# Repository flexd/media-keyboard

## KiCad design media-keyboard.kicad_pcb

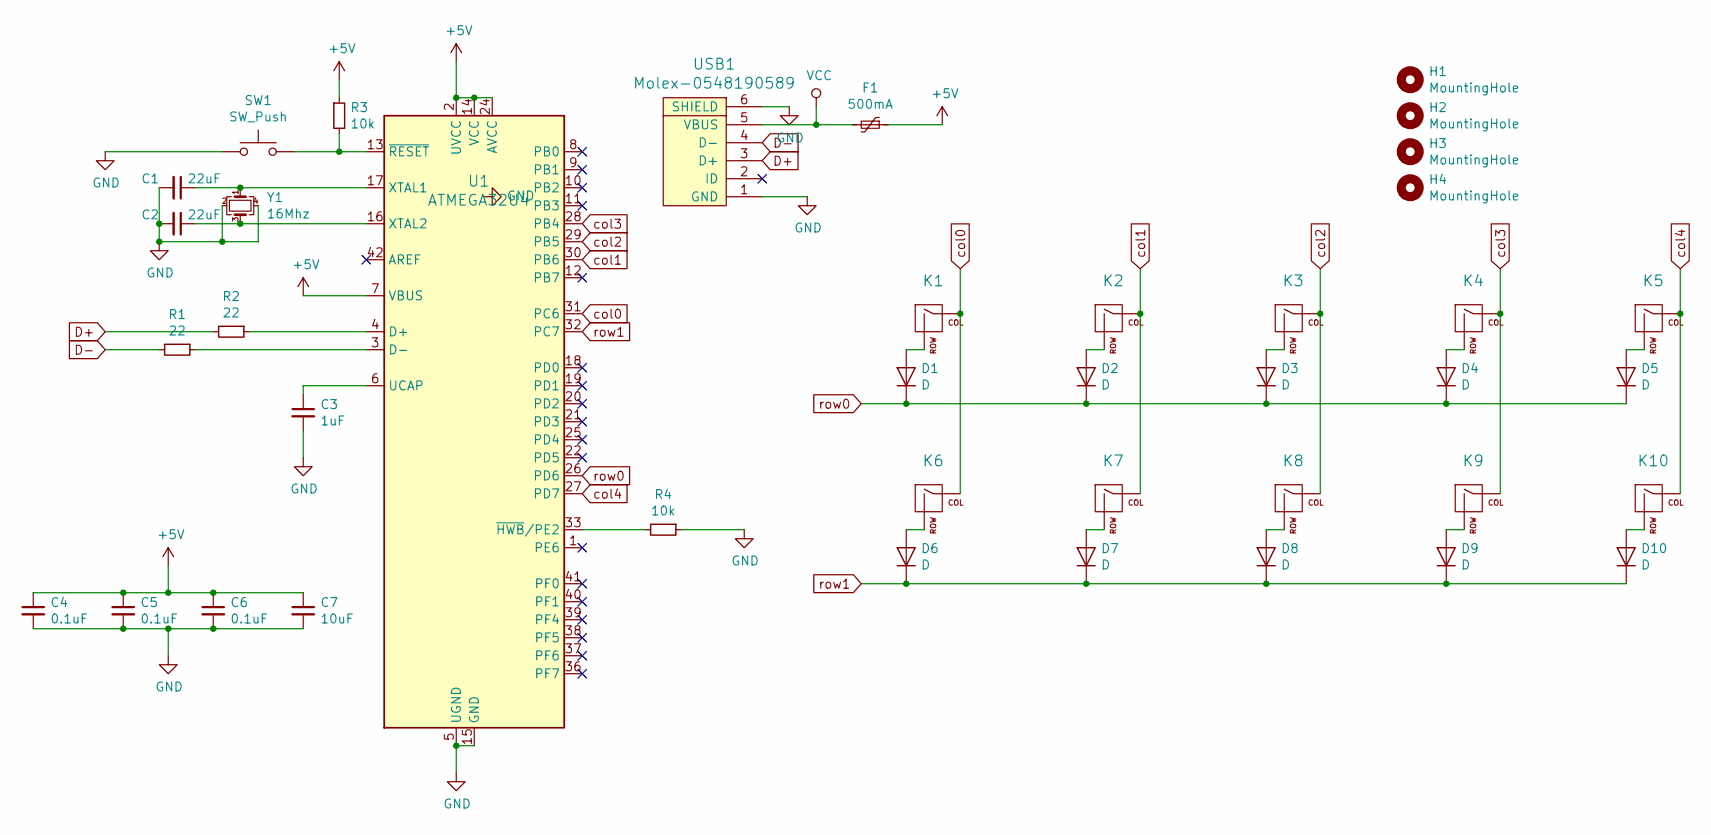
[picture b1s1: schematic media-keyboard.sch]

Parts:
C1, C2: 22uF; C_0805_2012Metric_Pad1.15x1.40mm_HandSolder
C3: 1uF; C_0805_2012Metric_Pad1.15x1.40mm_HandSolder
C4, C5, C6: 0.1uF; C_0805_2012Metric_Pad1.15x1.40mm_HandSolder
C7: 10uF; C_0805_2012Metric_Pad1.15x1.40mm_HandSolder
D1, D2, D3, D4, D5, D6, D7, D8, D9, D10: D; D_SOD-123
F1: 500mA; Fuse_1206_3216Metric
H1, H2, H3, H4: MountingHole; MountingHole_2.2mm_M2
K1, K2, K3, K4, K5, K6, K7, K8, K9, K10: KEYSW; MX-1U-NoLED
R1, R2: 22; R_0805_2012Metric_Pad1.15x1.40mm_HandSolder
R3, R4: 10k; R_0805_2012Metric_Pad1.15x1.40mm_HandSolder
SW1: SW_Push; SKQG-1155865
U1: ATMEGA32U4; TQFP-44_10x10mm_P0.8mm
USB1: Molex-0548190589
Y1: 16Mhz; Crystal_SMD_3225-4Pin_3.2x2.5mm

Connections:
+5V: C4.1, C5.1, C6.1, C7.1, F1.1, R3.1, U1.2 (UVCC), U1.7 (VBUS), U1.14 (VCC), U1.24 (AVCC), U1.34 (VCC), U1.44 (AVCC)
D+: R2.2, USB1.3 (D+)
D-: R1.2, USB1.4 (D-)
GND: C1.2, C2.2, C3.2, C4.2, C5.2, C6.2, C7.2, R4.1, SW1.1, U1.5 (UGND), U1.15 (GND), U1.23 (GND), U1.35 (GND), U1.43 (GND), USB1.1 (GND), USB1.6 (SHIELD), Y1.2, Y1.4
unnamed: C1.1, U1.17 (XTAL1), Y1.1
unnamed: C2.1, U1.16 (XTAL2), Y1.3
unnamed: C3.1, U1.6 (UCAP)
unnamed: D1.2 (A), K1.2 (ROW)
unnamed: D2.2 (A), K2.2 (ROW)
unnamed: D3.2 (A), K3.2 (ROW)
unnamed: D4.2 (A), K4.2 (ROW)
unnamed: D5.2 (A), K5.2 (ROW)
unnamed: D6.2 (A), K6.2 (ROW)
unnamed: D7.2 (A), K7.2 (ROW)
unnamed: D8.2 (A), K8.2 (ROW)
unnamed: D9.2 (A), K9.2 (ROW)
unnamed: D10.2 (A), K10.2 (ROW)
unnamed: R1.1, U1.3 (D-)
unnamed: R2.1, U1.4 (D+)
unnamed: R3.2, SW1.2, U1.13 (~RESET)
unnamed: R4.2, U1.33 (~HWB~/PE2)
VCC: F1.2, USB1.5 (VBUS)
col0: K1.1 (COL), K6.1 (COL), U1.31 (PC6)
col1: K2.1 (COL), K7.1 (COL), U1.30 (PB6)
col2: K3.1 (COL), K8.1 (COL), U1.29 (PB5)
col3: K4.1 (COL), K9.1 (COL), U1.28 (PB4)
col4: K5.1 (COL), K10.1 (COL), U1.27 (PD7)
row0: D1.1 (K), D2.1 (K), D3.1 (K), D4.1 (K), D5.1 (K), U1.26 (PD6)
row1: D6.1 (K), D7.1 (K), D8.1 (K), D9.1 (K), D10.1 (K), U1.32 (PC7)

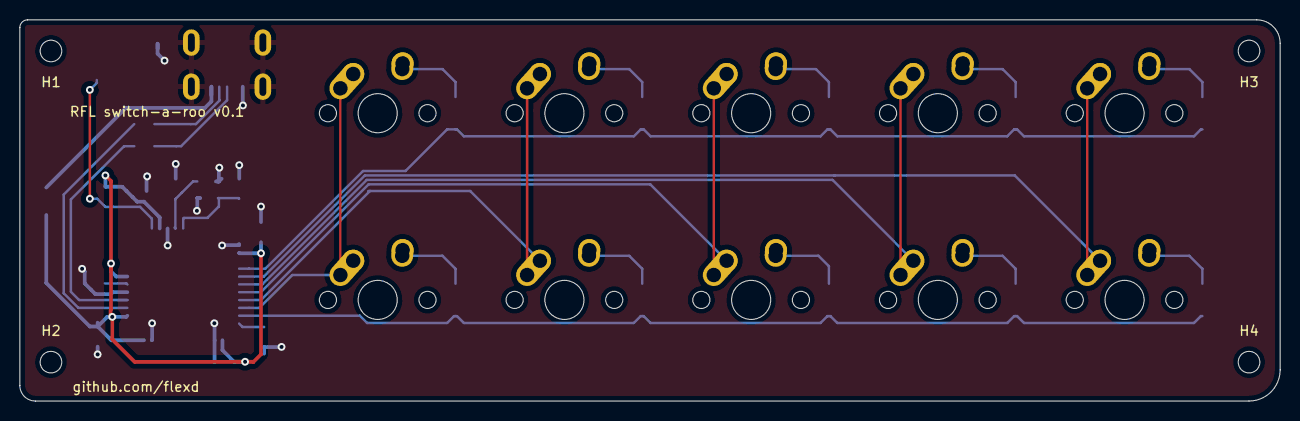
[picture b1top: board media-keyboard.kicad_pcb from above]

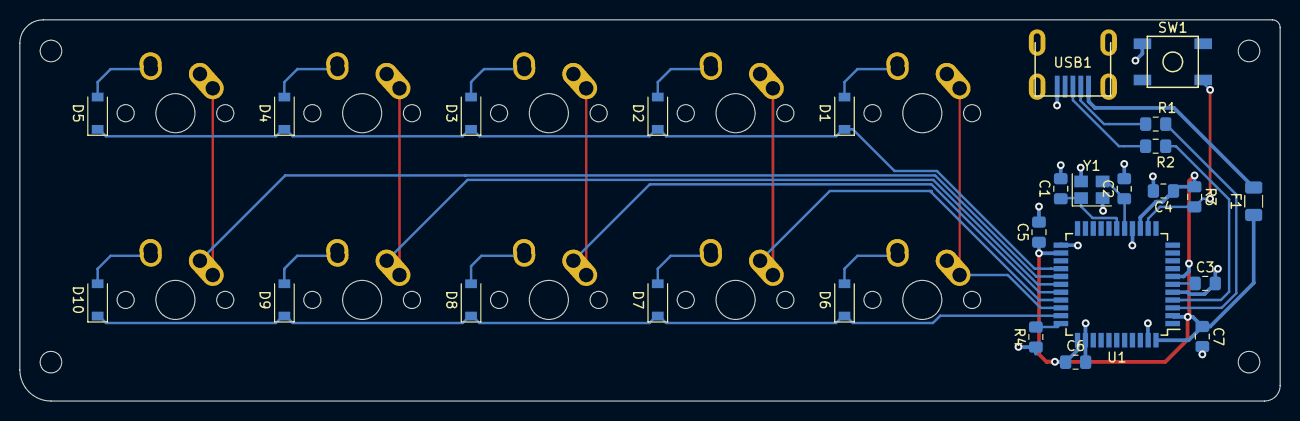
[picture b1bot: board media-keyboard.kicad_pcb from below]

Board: 2 copper layers, 128.6 x 38.9 mm, 40 parts (26 on the bottom side), 29 nets.

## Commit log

2019-08-29 Add submodules and .gitignore
2019-08-29 add a step 1 prototype to get started
2019-08-29 Add footprint and symbol libraries
2019-08-29 Schematic done!
2019-08-29 It should work!
2019-08-29 Some routing cleanup
2019-08-29 Even more cleanup
